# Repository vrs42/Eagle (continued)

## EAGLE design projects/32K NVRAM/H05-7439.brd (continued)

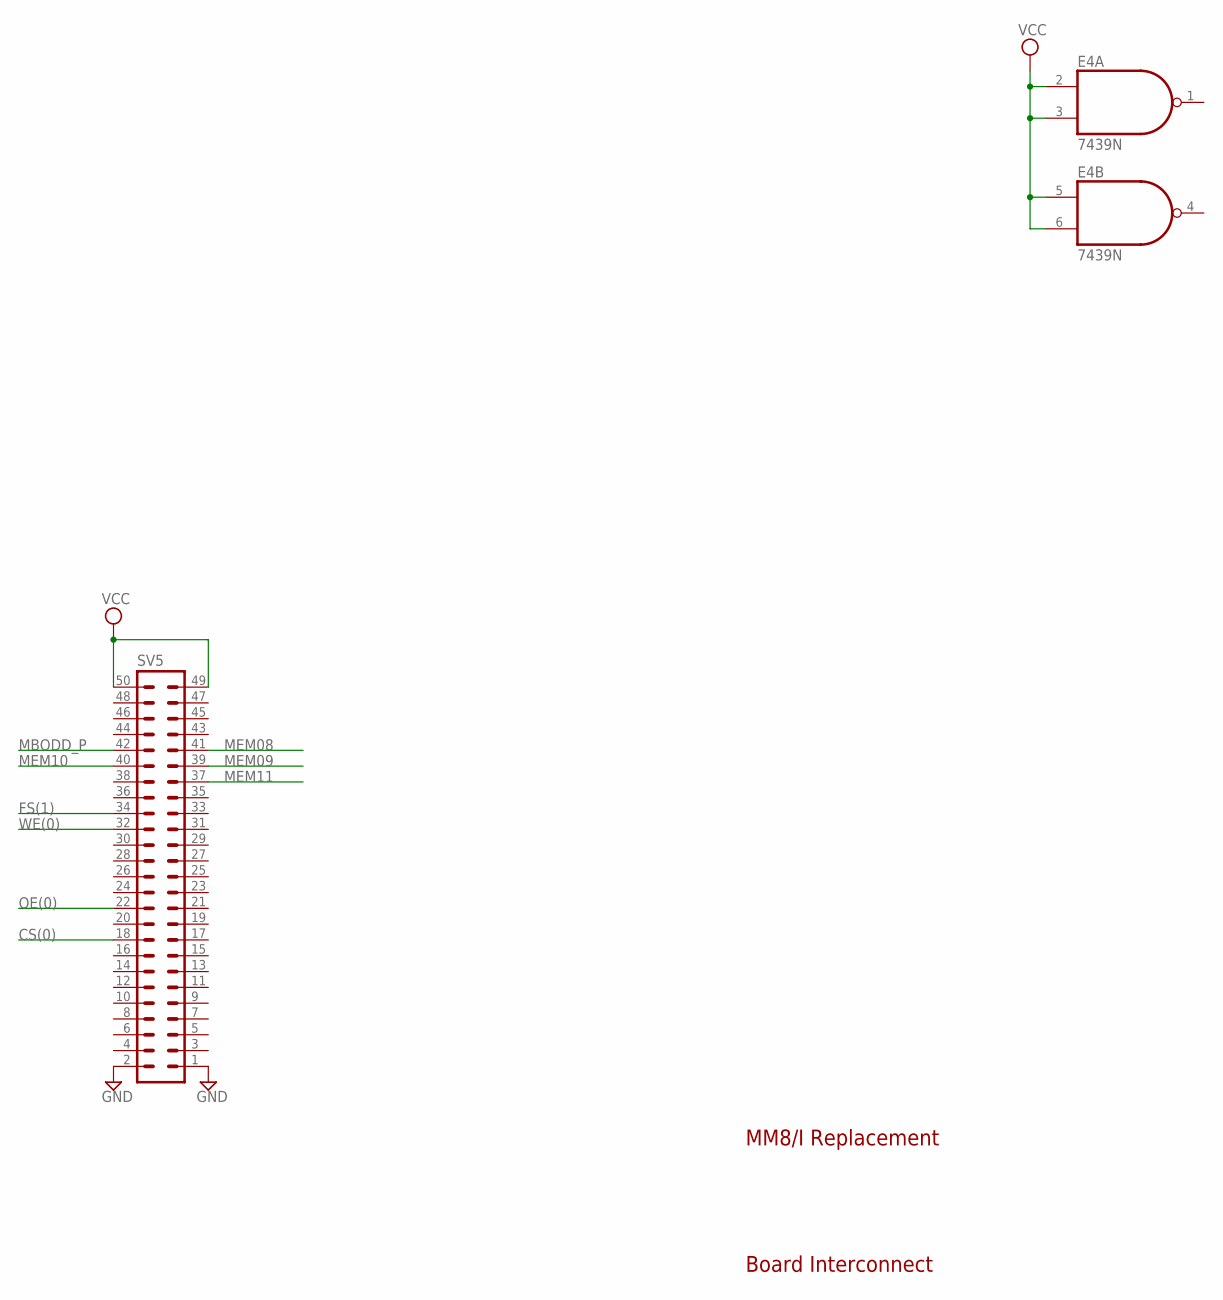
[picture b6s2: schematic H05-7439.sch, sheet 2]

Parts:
E4: 7439N; DIL14
SV5: ML50L

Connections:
CS(0): SV5.18; also elsewhere on the board
FS(1): SV5.34; also elsewhere on the board
GND: E4.7 (GND), SV5.1, SV5.2; also elsewhere on the board
MBODD_P: SV5.42; also elsewhere on the board
MEM08: SV5.41; also elsewhere on the board
MEM09: SV5.39; also elsewhere on the board
MEM10: SV5.40; also elsewhere on the board
MEM11: SV5.37; also elsewhere on the board
OE(0): SV5.22; also elsewhere on the board
VCC: E4.2 (I0), E4.3 (I1), E4.5 (I0), E4.6 (I1), E4.14 (VCC), SV5.49, SV5.50; also elsewhere on the board
WE(0): SV5.32; also elsewhere on the board

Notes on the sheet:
Board Interconnect
MM8/I Replacement

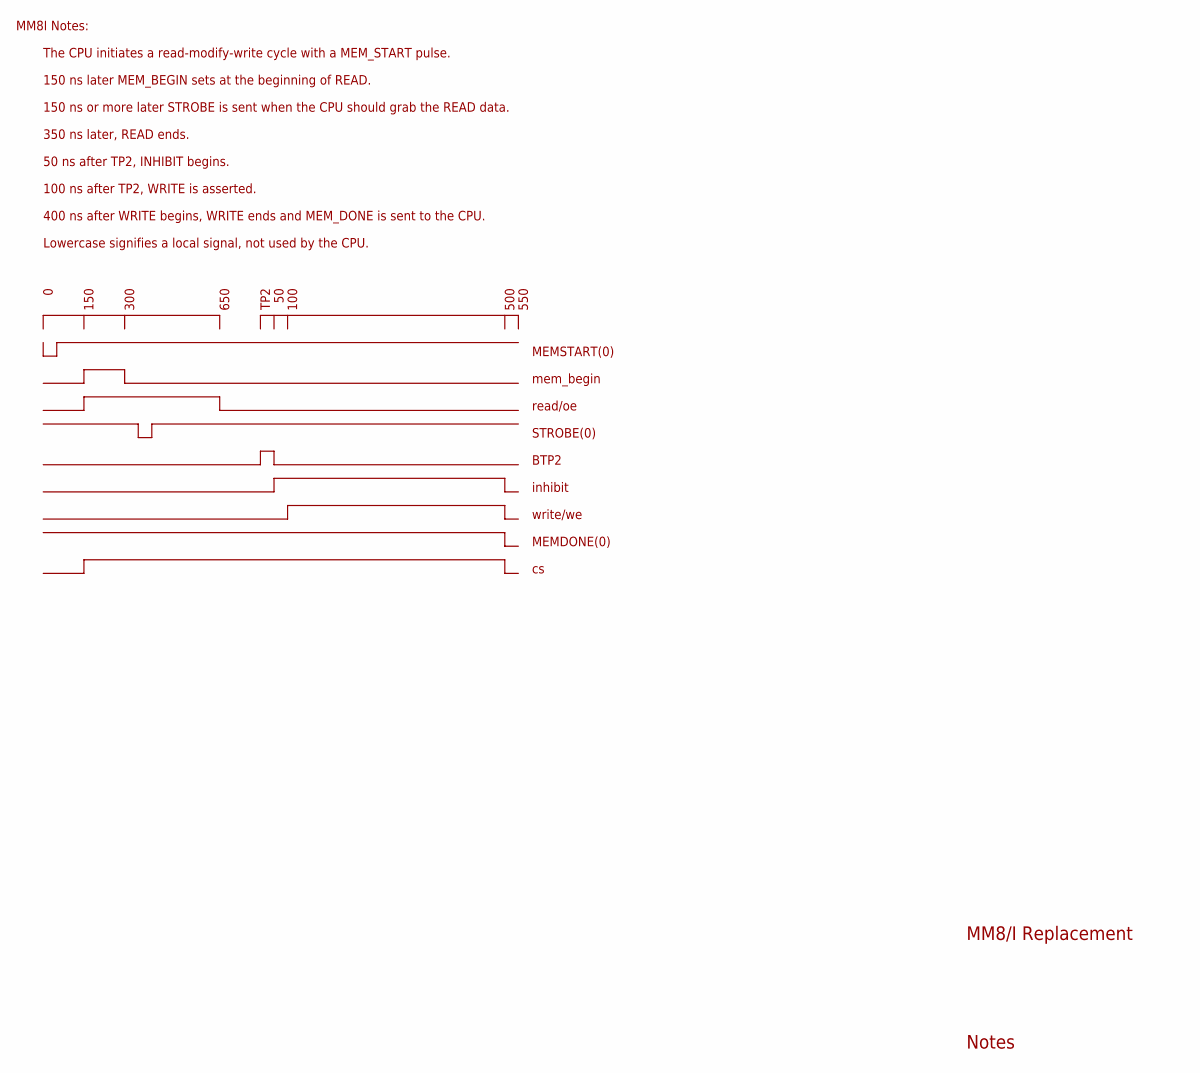
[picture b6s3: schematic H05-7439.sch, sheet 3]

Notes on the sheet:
Notes
The CPU initiates a read-modify-write cycle with a MEM_START pulse.
150 ns later MEM_BEGIN sets at the beginning of READ.
150 ns or more later STROBE is sent when the CPU should grab the READ data.
50 ns after TP2, INHIBIT begins.
100 ns after TP2, WRITE is asserted.
400 ns after WRITE begins, WRITE ends and MEM_DONE is sent to the CPU.
350 ns later, READ ends.
150
300
650
TP2
100
500
MEMSTART(0)
mem_begin
read/oe
STROBE(0)
BTP2
inhibit
write/we
MEMDONE(0)
Lowercase signifies a local signal, not used by the CPU.
550
MM8I Notes:
MM8/I Replacement

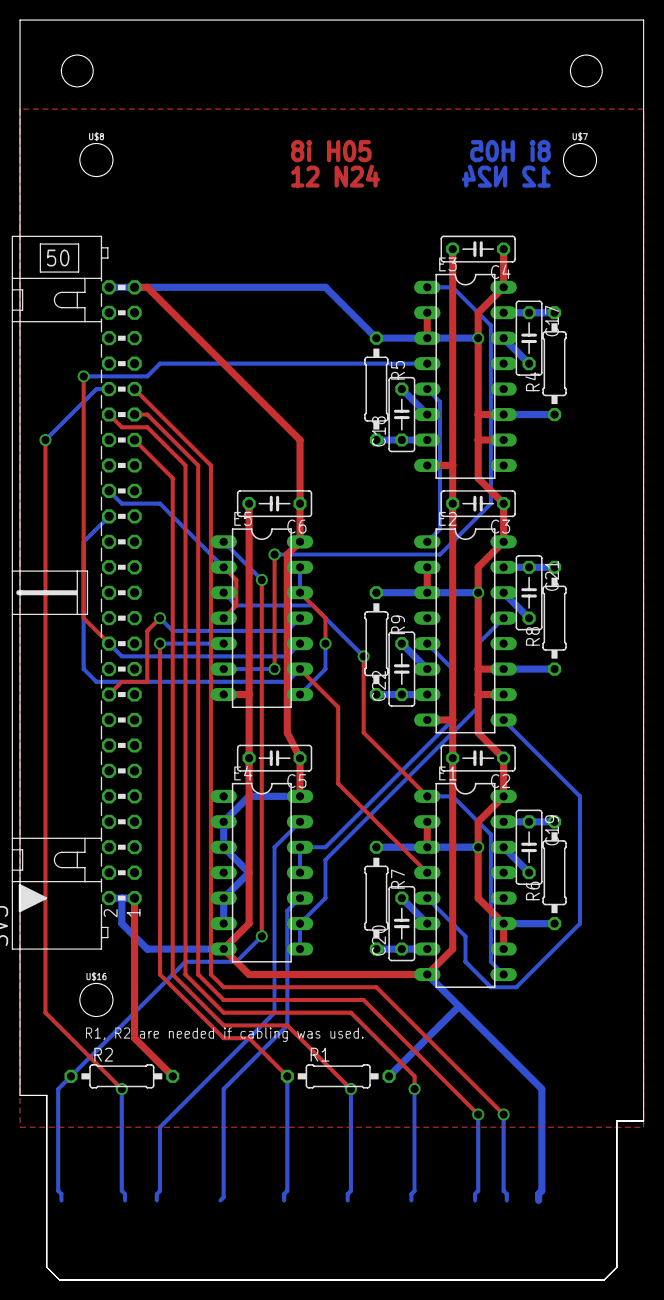
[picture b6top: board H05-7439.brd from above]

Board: 2 copper layers, 62.2 x 125.7 mm, 30 parts (0 on the bottom side), 34 nets.

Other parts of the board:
U$7, U$8, U$16: STAND-OFF

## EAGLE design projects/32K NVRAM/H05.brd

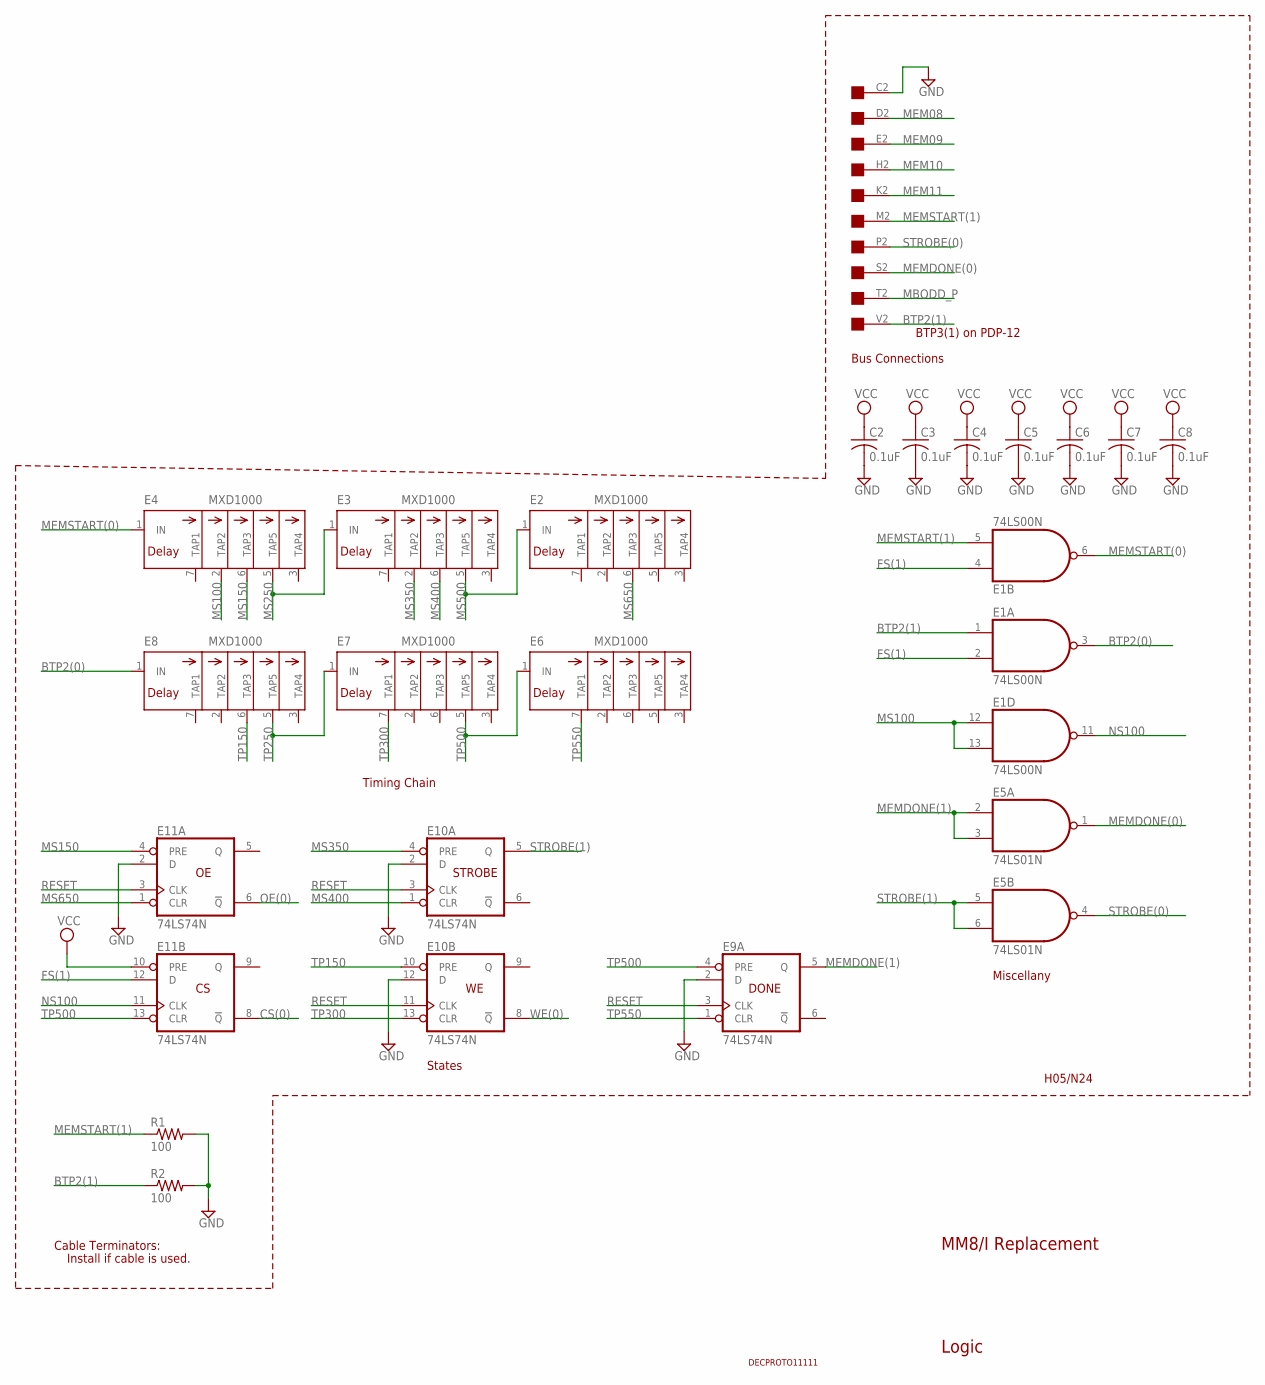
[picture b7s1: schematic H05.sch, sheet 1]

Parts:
C2, C3, C4, C5, C6, C7, C8: 0.1uF; C050-025X075
E1: 74LS00N; DIL14
E2, E3, E4, E6, E7, E8: MXD1000; DIL08
E5: 74LS01N; DIL14
E9, E10, E11: 74LS74N; DIL14
H05: EDGE-CON1
R1, R2: 100; 0207/10
U$6: DECPROTO11111

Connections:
BTP2(0): E1.3 (O), E8.1 (IN)
BTP2(1): E1.1 (I0), H05.V2, R2.1
CS(0): E11.8 (!Q); also elsewhere on the board
FS(1): E1.2 (I1), E1.4 (I0), E11.12 (D); also elsewhere on the board
GND: C2.2, C3.2, C4.2, C5.2, C6.2, C7.2, C8.2, E1.7 (GND), E2.4 (GND), E3.4 (GND), E4.4 (GND), E5.7 (GND), E6.4 (GND), E7.4 (GND), E8.4 (GND), E9.2 (D), E9.7 (GND), E10.2 (D), E10.7 (GND), E10.12 (D), E11.2 (D), E11.7 (GND), H05.C2, R1.2, R2.2; also elsewhere on the board
MBODD_P: H05.T2; also elsewhere on the board
MEM08: H05.D2; also elsewhere on the board
MEM09: H05.E2; also elsewhere on the board
MEM10: H05.H2; also elsewhere on the board
MEM11: H05.K2; also elsewhere on the board
MEMDONE(0): E5.1 (O), H05.S2
MEMDONE(1): E5.2 (I0), E5.3 (I1), E9.5 (Q)
MEMSTART(0): E1.6 (O), E4.1 (IN); also elsewhere on the board
MEMSTART(1): E1.5 (I1), H05.M2, R1.1
MS100: E1.12 (I0), E1.13 (I1), E4.2 (TAP2)
MS150: E4.6 (TAP3), E11.4 (PRE)
MS250: E3.1 (IN), E4.5 (TAP5)
MS350: E3.2 (TAP2), E10.4 (PRE)
MS400: E3.6 (TAP3), E10.1 (CLR)
MS500: E2.1 (IN), E3.5 (TAP5)
MS650: E2.6 (TAP3), E11.1 (CLR)
NS100: E1.11 (O), E11.11 (CLK)
OE(0): E11.6 (!Q); also elsewhere on the board
RESET: E9.3 (CLK), E10.3 (CLK), E10.11 (CLK), E11.3 (CLK); also elsewhere on the board
STROBE(0): E5.4 (O), H05.P2
STROBE(1): E5.5 (I0), E5.6 (I1), E10.5 (Q)
TP150: E8.6 (TAP3), E10.10 (PRE)
TP250: E7.1 (IN), E8.5 (TAP5)
TP300: E7.7 (TAP1), E10.13 (CLR)
TP500: E6.1 (IN), E7.5 (TAP5), E9.4 (PRE), E11.13 (CLR)
TP550: E6.7 (TAP1), E9.1 (CLR)
VCC: C2.1, C3.1, C4.1, C5.1, C6.1, C7.1, C8.1, E1.14 (VCC), E2.8 (VCC), E3.8 (VCC), E4.8 (VCC), E5.14 (VCC), E6.8 (VCC), E7.8 (VCC), E8.8 (VCC), E9.14 (VCC), E10.14 (VCC), E11.10 (PRE), E11.14 (VCC); also elsewhere on the board
WE(0): E10.8 (!Q); also elsewhere on the board

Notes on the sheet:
STROBE
DONE
MM8/I Replacement
Timing Chain
States
BTP3(1) on PDP-12
Miscellany
H05/N24
Logic
Bus Connections
Cable Terminators:
Install if cable is used.

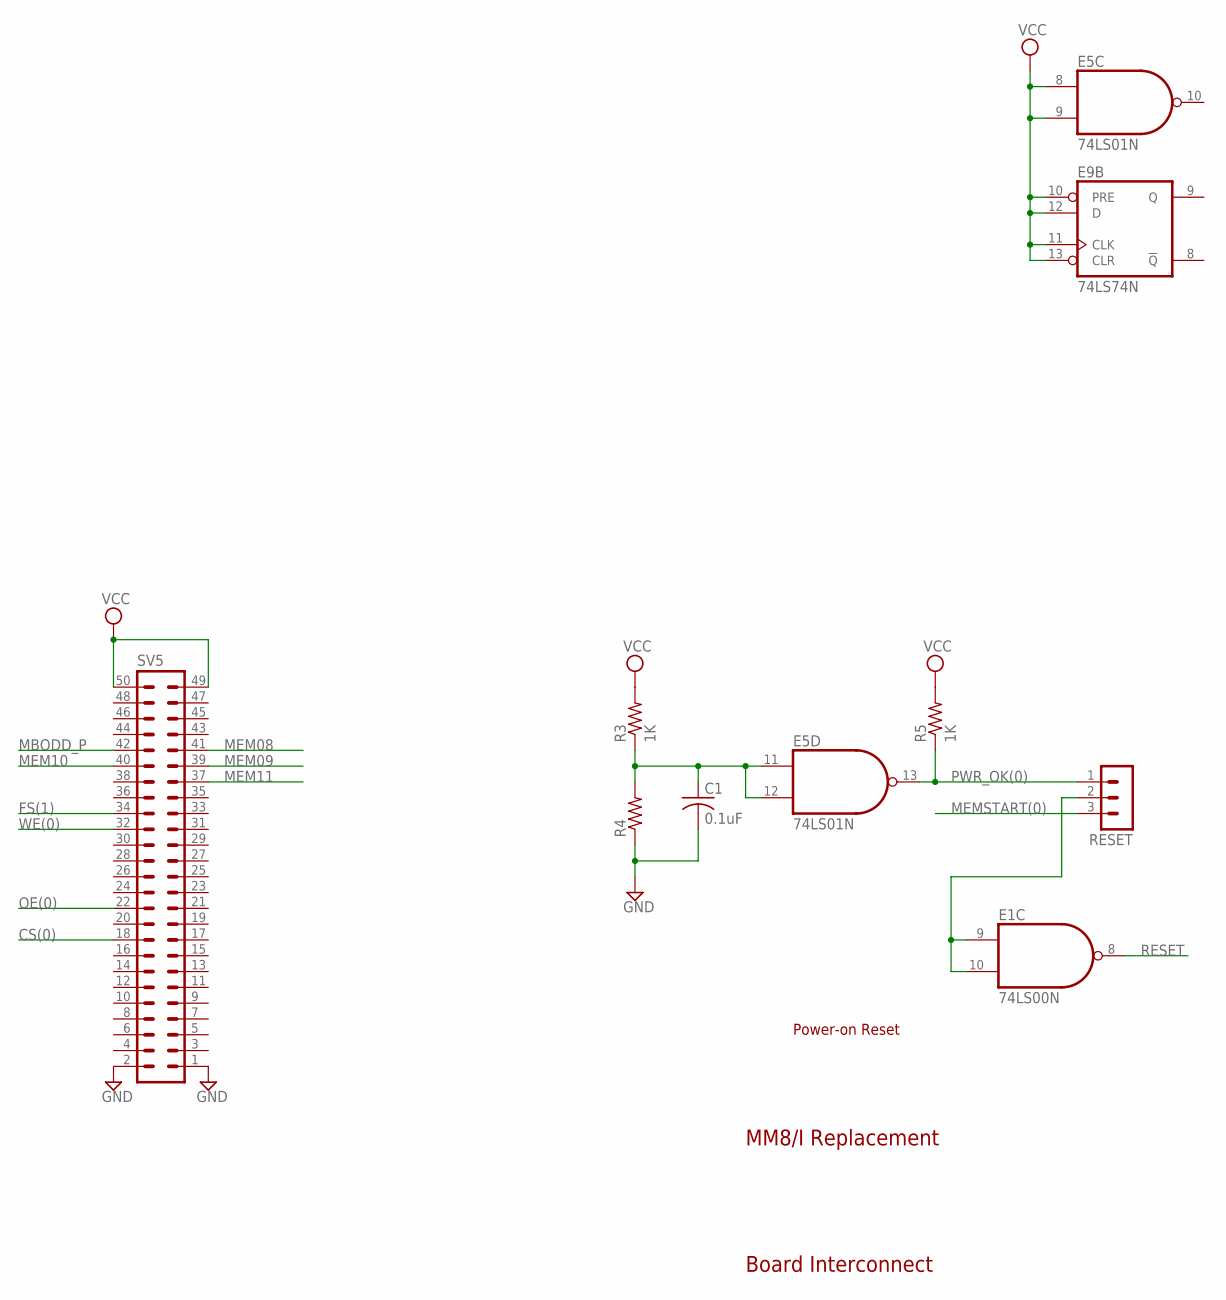
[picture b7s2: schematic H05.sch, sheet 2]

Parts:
C1: 0.1uF; C050-025X075
E1: 74LS00N; DIL14
E5: 74LS01N; DIL14
E9: 74LS74N; DIL14
R3, R5: 1K; 0207/10
R4: R-US_0207/10; 0207/10
RESET: MA03-1
SV5: ML50L

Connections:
CS(0): SV5.18; also elsewhere on the board
FS(1): SV5.34; also elsewhere on the board
GND: C1.2, E1.7 (GND), E5.7 (GND), E9.7 (GND), R4.1, SV5.1, SV5.2; also elsewhere on the board
MBODD_P: SV5.42; also elsewhere on the board
MEM08: SV5.41; also elsewhere on the board
MEM09: SV5.39; also elsewhere on the board
MEM10: SV5.40; also elsewhere on the board
MEM11: SV5.37; also elsewhere on the board
MEMSTART(0): RESET.3; also elsewhere on the board
unnamed: E1.9 (I0), E1.10 (I1), RESET.2
OE(0): SV5.22; also elsewhere on the board
PWR_OK: C1.1, E5.11 (I0), E5.12 (I1), R3.1, R4.2
PWR_OK(0): E5.13 (O), R5.1, RESET.1
RESET: E1.8 (O); also elsewhere on the board
VCC: E1.14 (VCC), E5.8 (I0), E5.9 (I1), E5.14 (VCC), E9.10 (PRE), E9.11 (CLK), E9.12 (D), E9.13 (CLR), E9.14 (VCC), R3.2, R5.2, SV5.49, SV5.50; also elsewhere on the board
WE(0): SV5.32; also elsewhere on the board

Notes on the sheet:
Board Interconnect
MM8/I Replacement
Power-on Reset

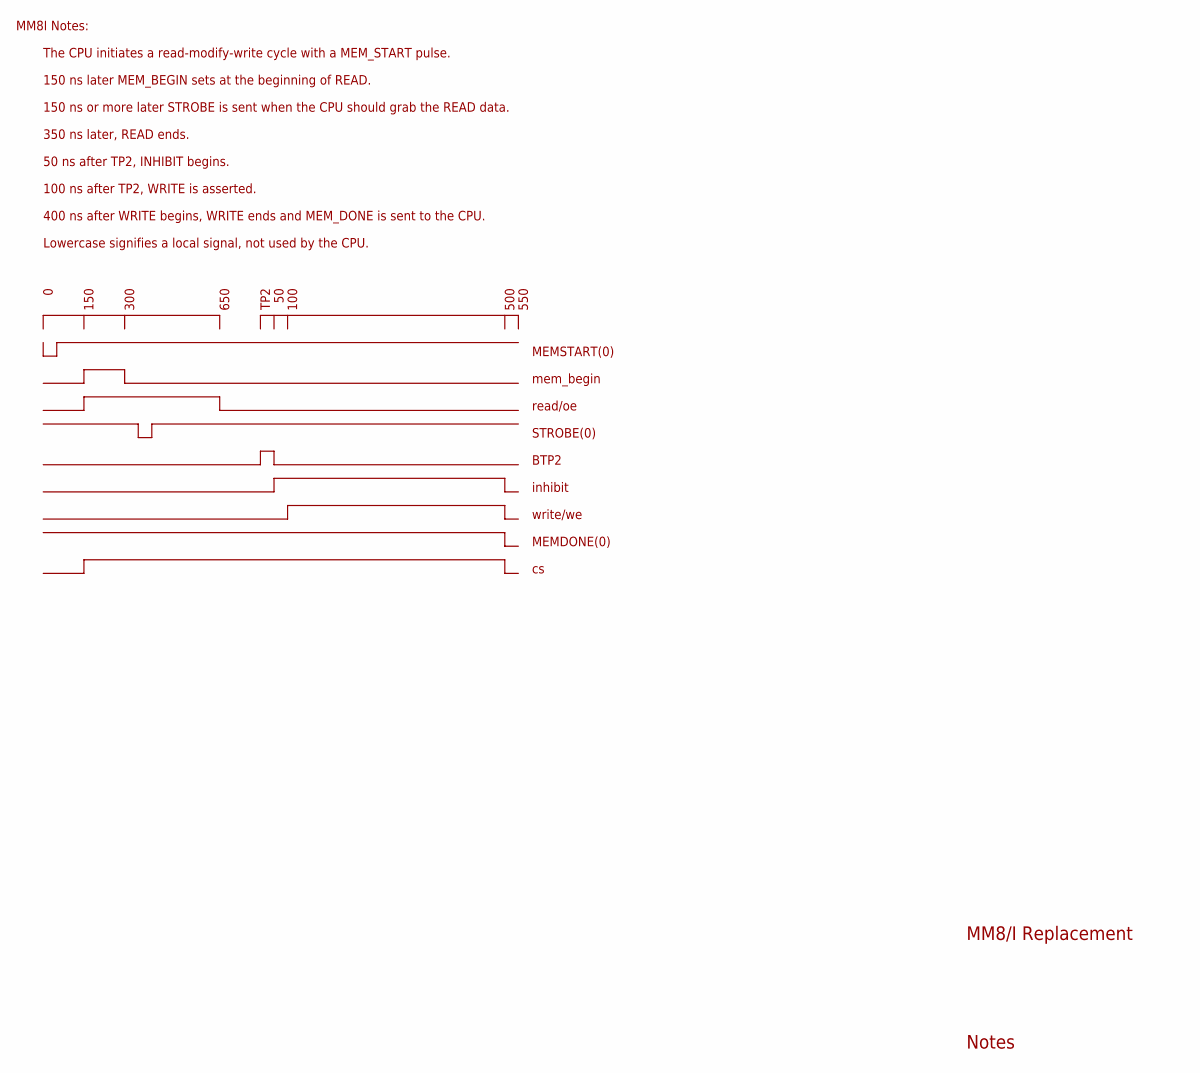
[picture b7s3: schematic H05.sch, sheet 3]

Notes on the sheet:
Notes
The CPU initiates a read-modify-write cycle with a MEM_START pulse.
150 ns later MEM_BEGIN sets at the beginning of READ.
150 ns or more later STROBE is sent when the CPU should grab the READ data.
50 ns after TP2, INHIBIT begins.
100 ns after TP2, WRITE is asserted.
400 ns after WRITE begins, WRITE ends and MEM_DONE is sent to the CPU.
350 ns later, READ ends.
150
300
650
TP2
100
500
MEMSTART(0)
mem_begin
read/oe
STROBE(0)
BTP2
inhibit
write/we
MEMDONE(0)
Lowercase signifies a local signal, not used by the CPU.
550
MM8I Notes:
MM8/I Replacement

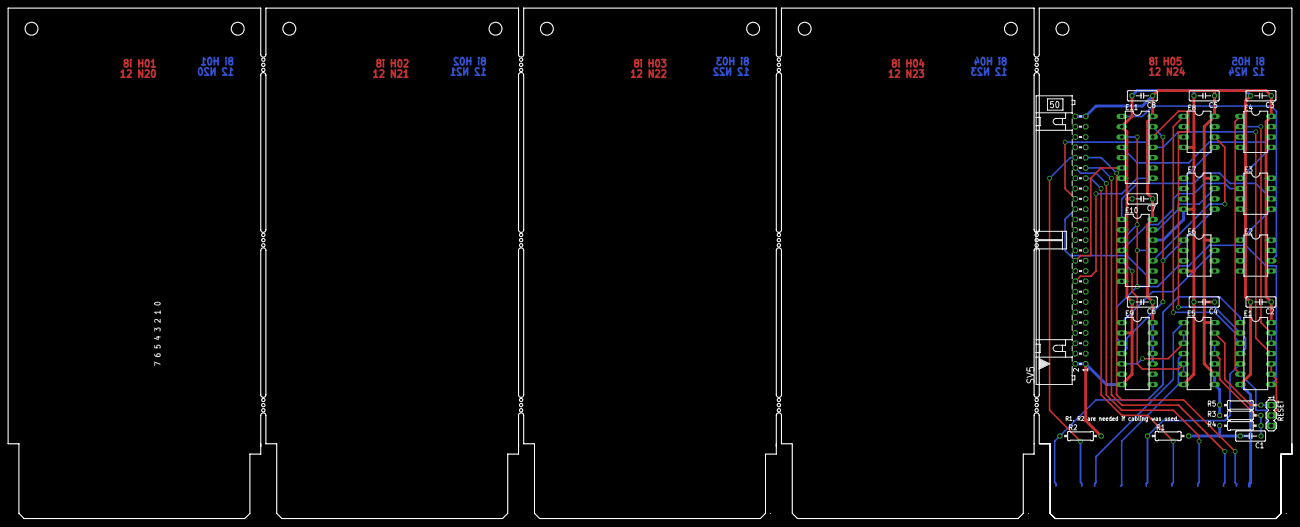
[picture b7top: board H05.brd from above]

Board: 2 copper layers, 316.2 x 125.7 mm, 28 parts (0 on the bottom side), 36 nets.

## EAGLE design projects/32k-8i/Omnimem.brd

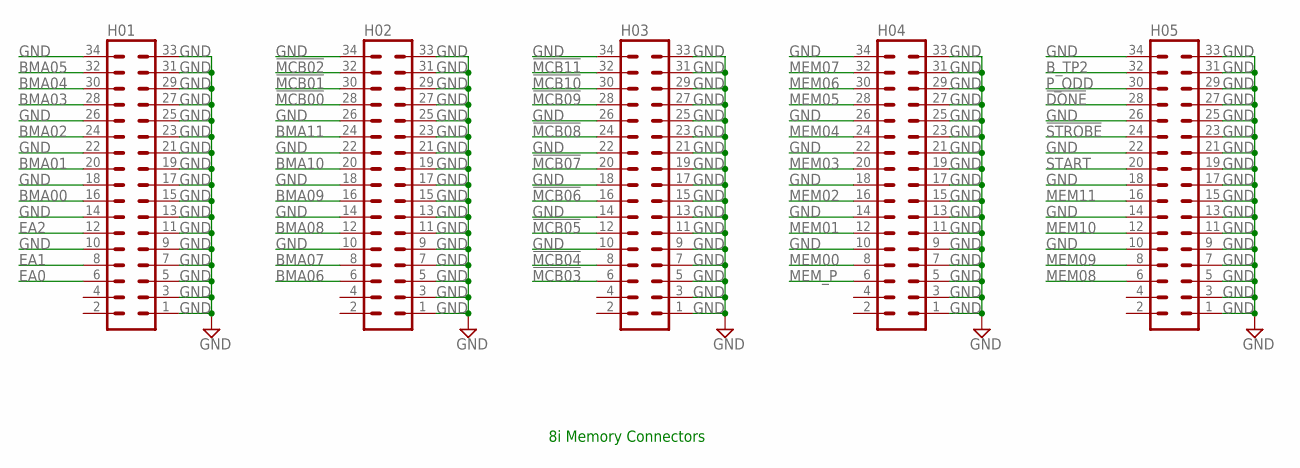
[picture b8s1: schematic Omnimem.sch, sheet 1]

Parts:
H01, H02, H03, H04, H05: MA17-2

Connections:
!DONE: H05.28
!MCB00: H02.28; also elsewhere on the board
!MCB01: H02.30; also elsewhere on the board
!MCB02: H02.32; also elsewhere on the board
!MCB03: H03.6; also elsewhere on the board
!MCB04: H03.8; also elsewhere on the board
!MCB05: H03.12; also elsewhere on the board
!MCB06: H03.16; also elsewhere on the board
!MCB07: H03.20; also elsewhere on the board
!MCB08: H03.24; also elsewhere on the board
!MCB09: H03.28; also elsewhere on the board
!MCB10: H03.30; also elsewhere on the board
!MCB11: H03.32; also elsewhere on the board
!STROBE: H05.24
BMA00: H01.16
BMA01: H01.20
BMA02: H01.24
BMA03: H01.28
BMA04: H01.30
BMA05: H01.32
BMA06: H02.6
BMA07: H02.8
BMA08: H02.12
BMA09: H02.16
BMA10: H02.20
BMA11: H02.24
B_TP2: H05.32
EA0: H01.6; also elsewhere on the board
EA1: H01.8; also elsewhere on the board
EA2: H01.12; also elsewhere on the board
GND: H01.1, H01.3, H01.5, H01.7, H01.9, H01.10, H01.11, H01.13, H01.14, H01.15, H01.17, H01.18, H01.19, H01.21, H01.22, H01.23, H01.25, H01.26, H01.27, H01.29, H01.31, H01.33, H01.34, H02.1, H02.3, H02.5, H02.7, H02.9, H02.10, H02.11, H02.13, H02.14, H02.15, H02.17, H02.18, H02.19, H02.21, H02.22, H02.23, H02.25, H02.26, H02.27, H02.29, H02.31, H02.33, H02.34, H03.1, H03.3, H03.5, H03.7, H03.9, H03.10, H03.11, H03.13, H03.14, H03.15, H03.17, H03.18, H03.19, H03.21, H03.22, H03.23, H03.25, H03.26, H03.27, H03.29, H03.31, H03.33, H03.34, H04.1, H04.3, H04.5, H04.7, H04.9, H04.10, H04.11, H04.13, H04.14, H04.15, H04.17, H04.18, H04.19, H04.21, H04.22, H04.23, H04.25, H04.26, H04.27, H04.29, H04.31, H04.33, H04.34, H05.1, H05.3, H05.5, H05.7, H05.9, H05.10, H05.11, H05.13, H05.14, H05.15, H05.17, H05.18, H05.19, H05.21, H05.22, H05.23, H05.25, H05.26, H05.27, H05.29, H05.31, H05.33, H05.34; also elsewhere on the board
MEM00: H04.8; also elsewhere on the board
MEM01: H04.12; also elsewhere on the board
MEM02: H04.16; also elsewhere on the board
MEM03: H04.20; also elsewhere on the board
MEM04: H04.24; also elsewhere on the board
MEM05: H04.28; also elsewhere on the board
MEM06: H04.30; also elsewhere on the board
MEM07: H04.32; also elsewhere on the board
MEM08: H05.6; also elsewhere on the board
MEM09: H05.8; also elsewhere on the board
MEM10: H05.12; also elsewhere on the board
MEM11: H05.16; also elsewhere on the board
MEM_P: H04.6
P_ODD: H05.30
START: H05.20

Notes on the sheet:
8i Memory Connectors

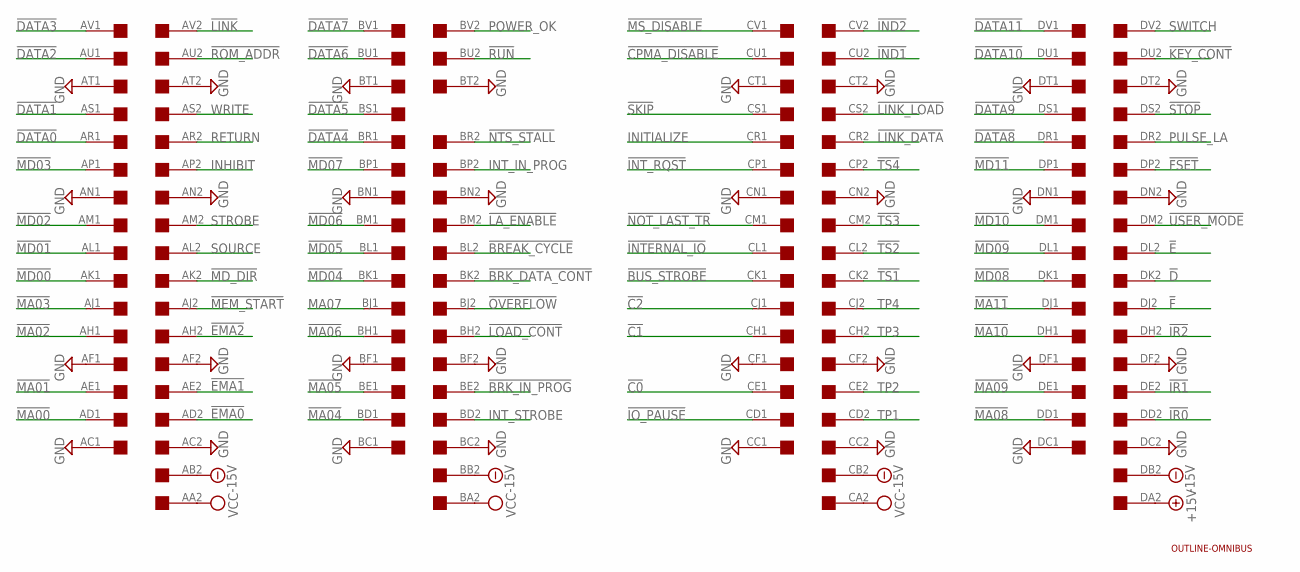
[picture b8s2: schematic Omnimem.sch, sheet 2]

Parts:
U$1: OUTLINE-OMNIBUS; OMNIBUS
U$2: QUAD; EDGE-CON8

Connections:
!BREAK_CYCLE: U$2.BL2
!BRK_DATA_CONT: U$2.BK2
!BRK_IN_PROG: U$2.BE2
!BUS_STROBE: U$2.CK1
!C0: U$2.CE1
!C1: U$2.CH1
!C2: U$2.CJ1
!CPMA_DISABLE: U$2.CU1
!D: U$2.DK2
!DATA0: U$2.AR1
!DATA1: U$2.AS1
!DATA2: U$2.AU1
!DATA3: U$2.AV1
!DATA4: U$2.BR1
!DATA5: U$2.BS1
!DATA6: U$2.BU1
!DATA7: U$2.BV1
!DATA8: U$2.DR1
!DATA9: U$2.DS1
!DATA10: U$2.DU1
!DATA11: U$2.DV1
!E: U$2.DL2
!EMA0: U$2.AD2
!EMA1: U$2.AE2
!EMA2: U$2.AH2
!F: U$2.DJ2
!FSET: U$2.DP2
!IND1: U$2.CU2
!IND2: U$2.CV2
!INTERNAL_IO: U$2.CL1
!INT_RQST: U$2.CP1
!IO_PAUSE: U$2.CD1
!IR0: U$2.DD2
!IR1: U$2.DE2
!IR2: U$2.DH2
!KEY_CONT: U$2.DU2
!LA_ENABLE: U$2.BM2
!LINK: U$2.AV2
!LINK_DATA: U$2.CR2
!LINK_LOAD: U$2.CS2
!LOAD_CONT: U$2.BH2
!MA00: U$2.AD1
!MA01: U$2.AE1
!MA02: U$2.AH1
!MA03: U$2.AJ1
!MA04: U$2.BD1
!MA05: U$2.BE1
!MA06: U$2.BH1
!MA08: U$2.DD1
!MA09: U$2.DE1
!MA10: U$2.DH1
!MA11: U$2.DJ1
!MD00: U$2.AK1; also elsewhere on the board
!MD01: U$2.AL1; also elsewhere on the board
!MD02: U$2.AM1; also elsewhere on the board
!MD03: U$2.AP1; also elsewhere on the board
!MD04: U$2.BK1; also elsewhere on the board
!MD05: U$2.BL1; also elsewhere on the board
!MD06: U$2.BM1; also elsewhere on the board
!MD07: U$2.BP1; also elsewhere on the board
!MD08: U$2.DK1; also elsewhere on the board
!MD09: U$2.DL1; also elsewhere on the board
!MD10: U$2.DM1; also elsewhere on the board
!MD11: U$2.DP1; also elsewhere on the board
!MD_DIR: U$2.AK2; also elsewhere on the board
!MEM_START: U$2.AJ2
!MS_DISABLE: U$2.CV1
!NOT_LAST_TR: U$2.CM1
!NTS_STALL: U$2.BR2
!OVERFLOW: U$2.BJ2
!ROM_ADDR: U$2.AU2
!RUN: U$2.BU2
!SKIP: U$2.CS1
!STOP: U$2.DS2
!TS1: U$2.CK2
!TS2: U$2.CL2
!TS3: U$2.CM2
!TS4: U$2.CP2
!USER_MODE: U$2.DM2
+15V: U$2.DA2
-15V: U$2.AB2, U$2.BB2, U$2.CB2, U$2.DB2
GND: U$2.AC1, U$2.AC2, U$2.AF1, U$2.AF2, U$2.AN1, U$2.AN2, U$2.AT1, U$2.AT2, U$2.BC1, U$2.BC2, U$2.BF1, U$2.BF2, U$2.BN1, U$2.BN2, U$2.BT1, U$2.BT2, U$2.CC1, U$2.CC2, U$2.CF1, U$2.CF2, U$2.CN1, U$2.CN2, U$2.CT1, U$2.CT2, U$2.DC1, U$2.DC2, U$2.DF1, U$2.DF2, U$2.DN1, U$2.DN2, U$2.DT1, U$2.DT2; also elsewhere on the board
INHIBIT: U$2.AP2
INITIALIZE: U$2.CR1
INT_IN_PROG: U$2.BP2
INT_STROBE: U$2.BD2
MA07: U$2.BJ1
POWER_OK: U$2.BV2
PULSE_LA: U$2.DR2
RETURN: U$2.AR2
SOURCE: U$2.AL2
STROBE: U$2.AM2
SWITCH: U$2.DV2
TP1: U$2.CD2
TP2: U$2.CE2
TP3: U$2.CH2
TP4: U$2.CJ2
VCC: U$2.AA2, U$2.BA2, U$2.CA2; also elsewhere on the board
WRITE: U$2.AS2

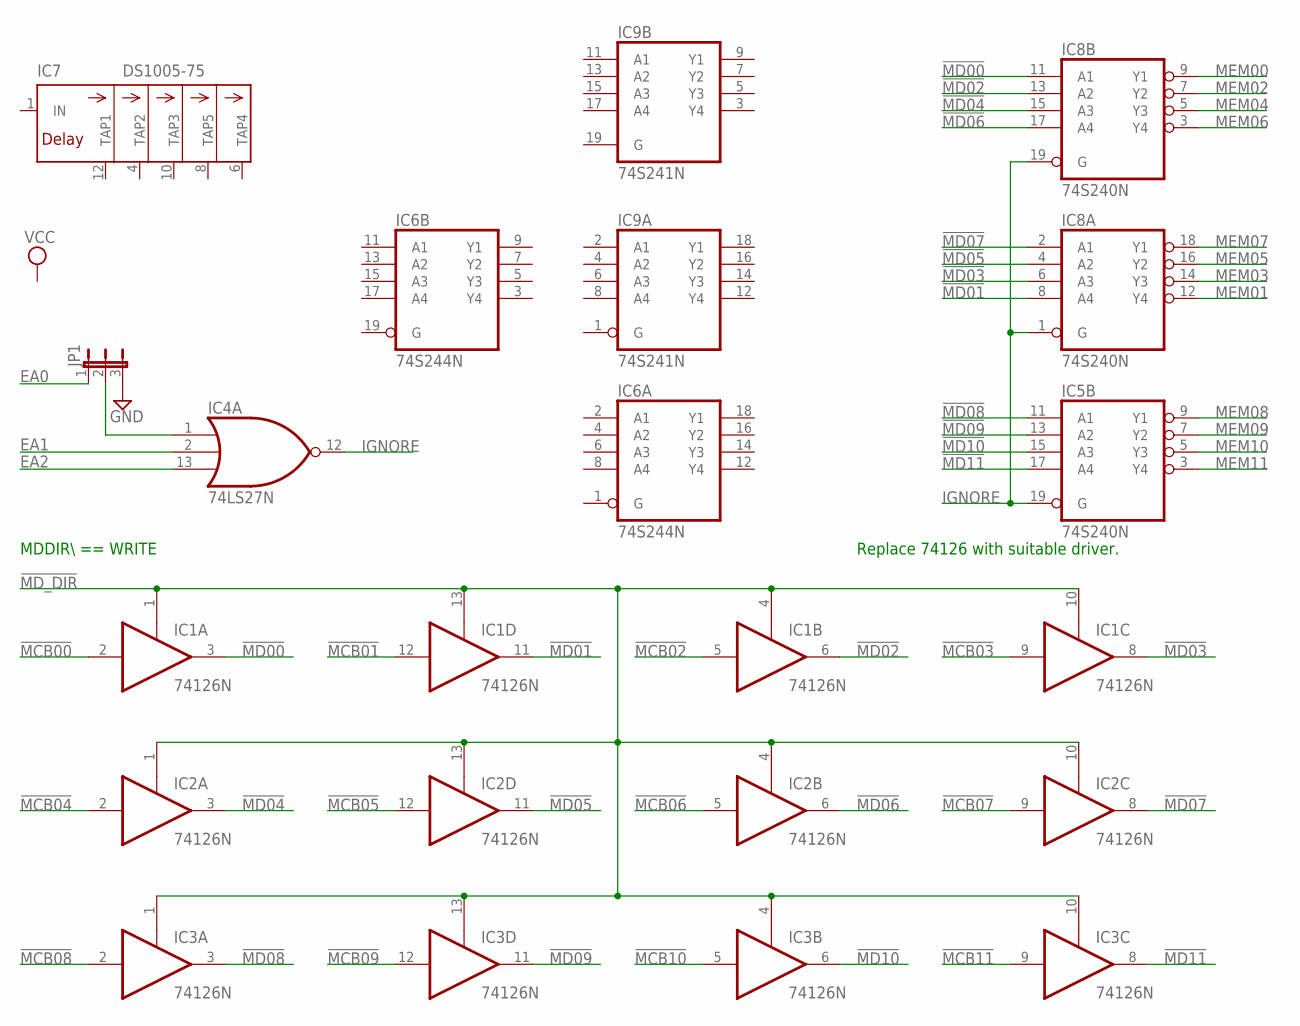
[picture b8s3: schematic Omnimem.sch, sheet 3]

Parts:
IC1, IC2, IC3: 74126N; DIL14
IC4: 74LS27N; DIL14
IC5, IC8: 74S240N; DIL20
IC6: 74S244N; DIL20
IC7: DS1005-75; DIL14
IC9: 74S241N; DIL20
JP1: JP2E; JP2

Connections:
!MCB00: IC1.2 (I); also elsewhere on the board
!MCB01: IC1.12 (I); also elsewhere on the board
!MCB02: IC1.5 (I); also elsewhere on the board
!MCB03: IC1.9 (I); also elsewhere on the board
!MCB04: IC2.2 (I); also elsewhere on the board
!MCB05: IC2.12 (I); also elsewhere on the board
!MCB06: IC2.5 (I); also elsewhere on the board
!MCB07: IC2.9 (I); also elsewhere on the board
!MCB08: IC3.2 (I); also elsewhere on the board
!MCB09: IC3.12 (I); also elsewhere on the board
!MCB10: IC3.5 (I); also elsewhere on the board
!MCB11: IC3.9 (I); also elsewhere on the board
!MD00: IC1.3 (O), IC8.11 (A1); also elsewhere on the board
!MD01: IC1.11 (O), IC8.8 (A4); also elsewhere on the board
!MD02: IC1.6 (O), IC8.13 (A2); also elsewhere on the board
!MD03: IC1.8 (O), IC8.6 (A3); also elsewhere on the board
!MD04: IC2.3 (O), IC8.15 (A3); also elsewhere on the board
!MD05: IC2.11 (O), IC8.4 (A2); also elsewhere on the board
!MD06: IC2.6 (O), IC8.17 (A4); also elsewhere on the board
!MD07: IC2.8 (O), IC8.2 (A1); also elsewhere on the board
!MD08: IC3.3 (O), IC5.11 (A1); also elsewhere on the board
!MD09: IC3.11 (O), IC5.13 (A2); also elsewhere on the board
!MD10: IC3.6 (O), IC5.15 (A3); also elsewhere on the board
!MD11: IC3.8 (O), IC5.17 (A4); also elsewhere on the board
!MD_DIR: IC1.1 (OE), IC1.4 (OE), IC1.10 (OE), IC1.13 (OE), IC2.1 (OE), IC2.4 (OE), IC2.10 (OE), IC2.13 (OE), IC3.1 (OE), IC3.4 (OE), IC3.10 (OE), IC3.13 (OE); also elsewhere on the board
EA0: JP1.1; also elsewhere on the board
EA1: IC4.2 (I1); also elsewhere on the board
EA2: IC4.13 (I2); also elsewhere on the board
GND: IC1.7 (GND), IC2.7 (GND), IC3.7 (GND), IC4.7 (GND), IC5.10 (GND), IC6.10 (GND), IC7.7 (GND), IC8.10 (GND), IC9.10 (GND), JP1.3; also elsewhere on the board
IGNORE: IC4.12 (O), IC5.19 (G), IC8.1 (G), IC8.19 (G)
MEM00: IC8.9 (Y1); also elsewhere on the board
MEM01: IC8.12 (Y4); also elsewhere on the board
MEM02: IC8.7 (Y2); also elsewhere on the board
MEM03: IC8.14 (Y3); also elsewhere on the board
MEM04: IC8.5 (Y3); also elsewhere on the board
MEM05: IC8.16 (Y2); also elsewhere on the board
MEM06: IC8.3 (Y4); also elsewhere on the board
MEM07: IC8.18 (Y1); also elsewhere on the board
MEM08: IC5.9 (Y1); also elsewhere on the board
MEM09: IC5.7 (Y2); also elsewhere on the board
MEM10: IC5.5 (Y3); also elsewhere on the board
MEM11: IC5.3 (Y4); also elsewhere on the board
unnamed: IC4.1 (I0), JP1.2
VCC: IC1.14 (VCC), IC2.14 (VCC), IC3.14 (VCC), IC4.14 (VCC), IC5.20 (VCC), IC6.20 (VCC), IC7.14 (VCC), IC8.20 (VCC), IC9.20 (VCC); also elsewhere on the board

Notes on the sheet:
MDDIR\\ == WRITE
Replace 74126 with suitable driver.

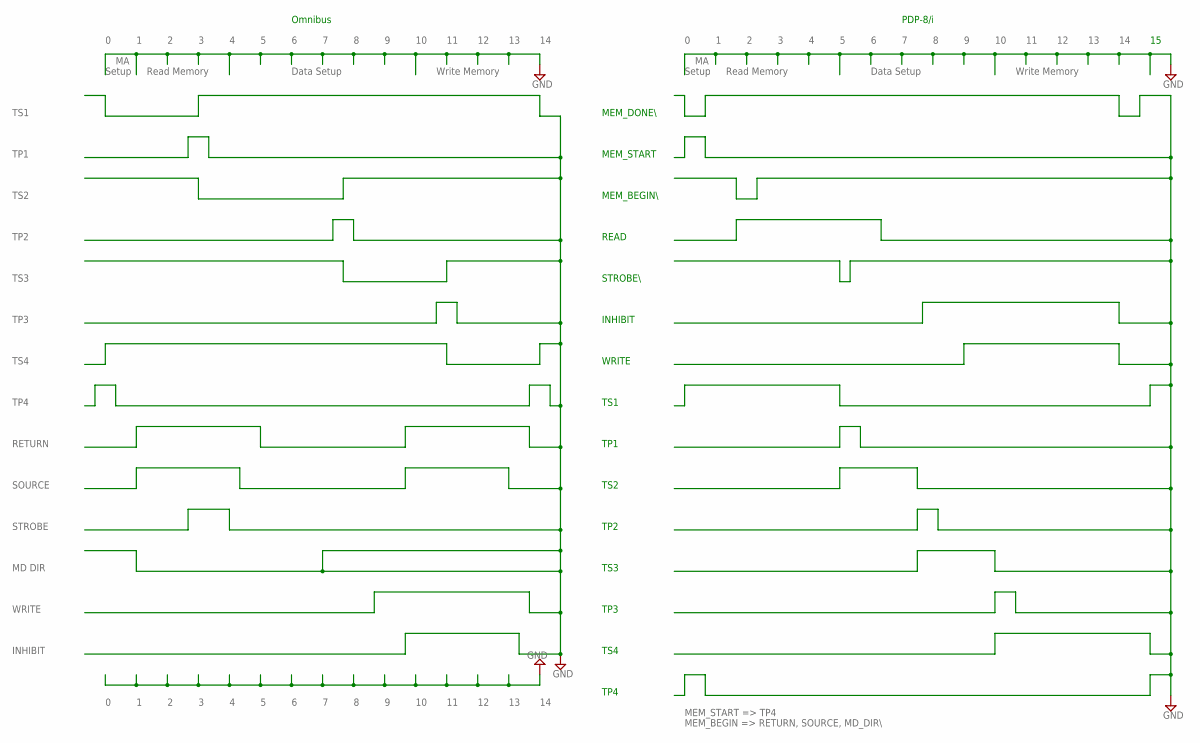
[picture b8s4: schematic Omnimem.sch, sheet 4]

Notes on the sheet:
MEM_DONE\\
MEM_START
MEM_BEGIN\\
READ
STROBE\\
INHIBIT
WRITE
TS1
TS2
TS3
TS4
TP1
TP2
TP3
TP4
STROBE
SOURCE
RETURN
MD DIR
Setup
Read Memory
Data Setup
Write Memory
MEM_START => TP4
MEM_BEGIN => RETURN, SOURCE, MD_DIR\\
Omnibus
PDP-8/i

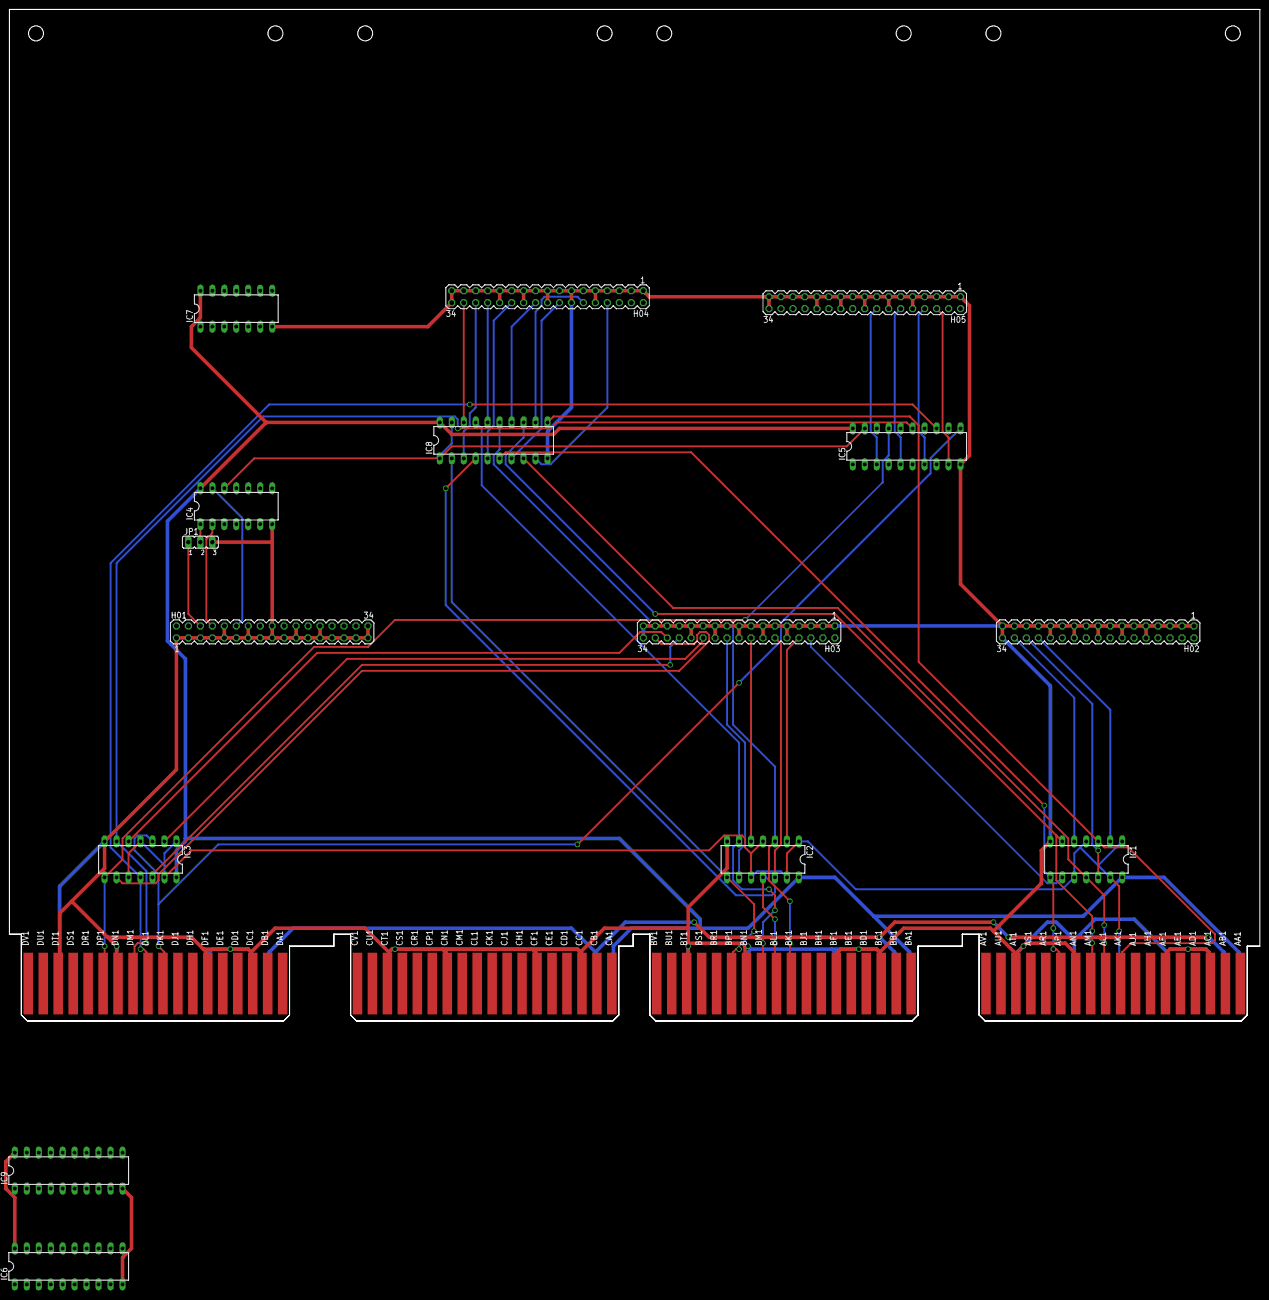
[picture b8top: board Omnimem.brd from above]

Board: 2 copper layers, 265.3 x 214.6 mm, 17 parts (0 on the bottom side), 45 nets.
